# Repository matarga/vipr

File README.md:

# What is VIPR?

Simply put, VIPR is a open source radio node designed and built around North American mesh communication over LoRa built off of an ESP32-S3 platform. Put less simply, VIPR is another ESP32 development board focused more on frontend, hardware, and size. The project aims to create a small, pocketable radio node that can run independently. Currently the procsessing power of it's latest version (2.0) can only handle small workloads and can only run a Real Time OS in comparison to a fully fledged computer.

**VIPR is currently in Alpha testing, soon to be beta!**

I'm planning on spinning this project idea and base into another, thinking aboutthe name of ProtopadZero

## Current Revision

Currently the board packs a 19mm wide footprint without a screen. The end is equipped with an SMA conector for easy antenna swaps and the side boasts an onboard PCB wifi antenna tied to the ESP32-MINI-1 module.

Future revisions intend to add a screen and interactives to the board to further refine the frontend, all that is needed after that is software and a case!

### Changelog

```
* Redid a proper BOM
    * This included sizing and components selection
* Added back the CH340X
* Reverted to old "pen" form factor
* Created a new "lopsided" board end 
* Added a screen header
* Fixed a regulator issue on the radio portion
* bundled CAD files into production folders <=2.1
* Added JTAG test pads for rev 2.1.1
```

## Docs

Docs will be coming soon!
<br>

## Versioning system

The project follows a versioning system of major and minor. The first number in the version is the board platform. Whenever the board is fully redone a new major version will be released. Whenever the board has a small tweak to an existing platform version the second number behind the first will be bumped up by one.

A board version of say, 2.1 would indicate platform version 2 with one tweak of the original version 2.0.

#### Latest Journal as of July 28th

For revision 2.1. I introduced a versioning system of major and minor.
 What's new in 2.1?

Mounting holes for M2 screws on the left side of the board and a header connection for a screen. the schematics now include test points for serial, power, and JTAG soon to be onboard for revision 2.2.

Some issues were included in revision 2 that would prevent stable operation of the radio caused by a faulty connection between the regulator for the SX1262 and the inductor managing it.

That's all.

-Matias

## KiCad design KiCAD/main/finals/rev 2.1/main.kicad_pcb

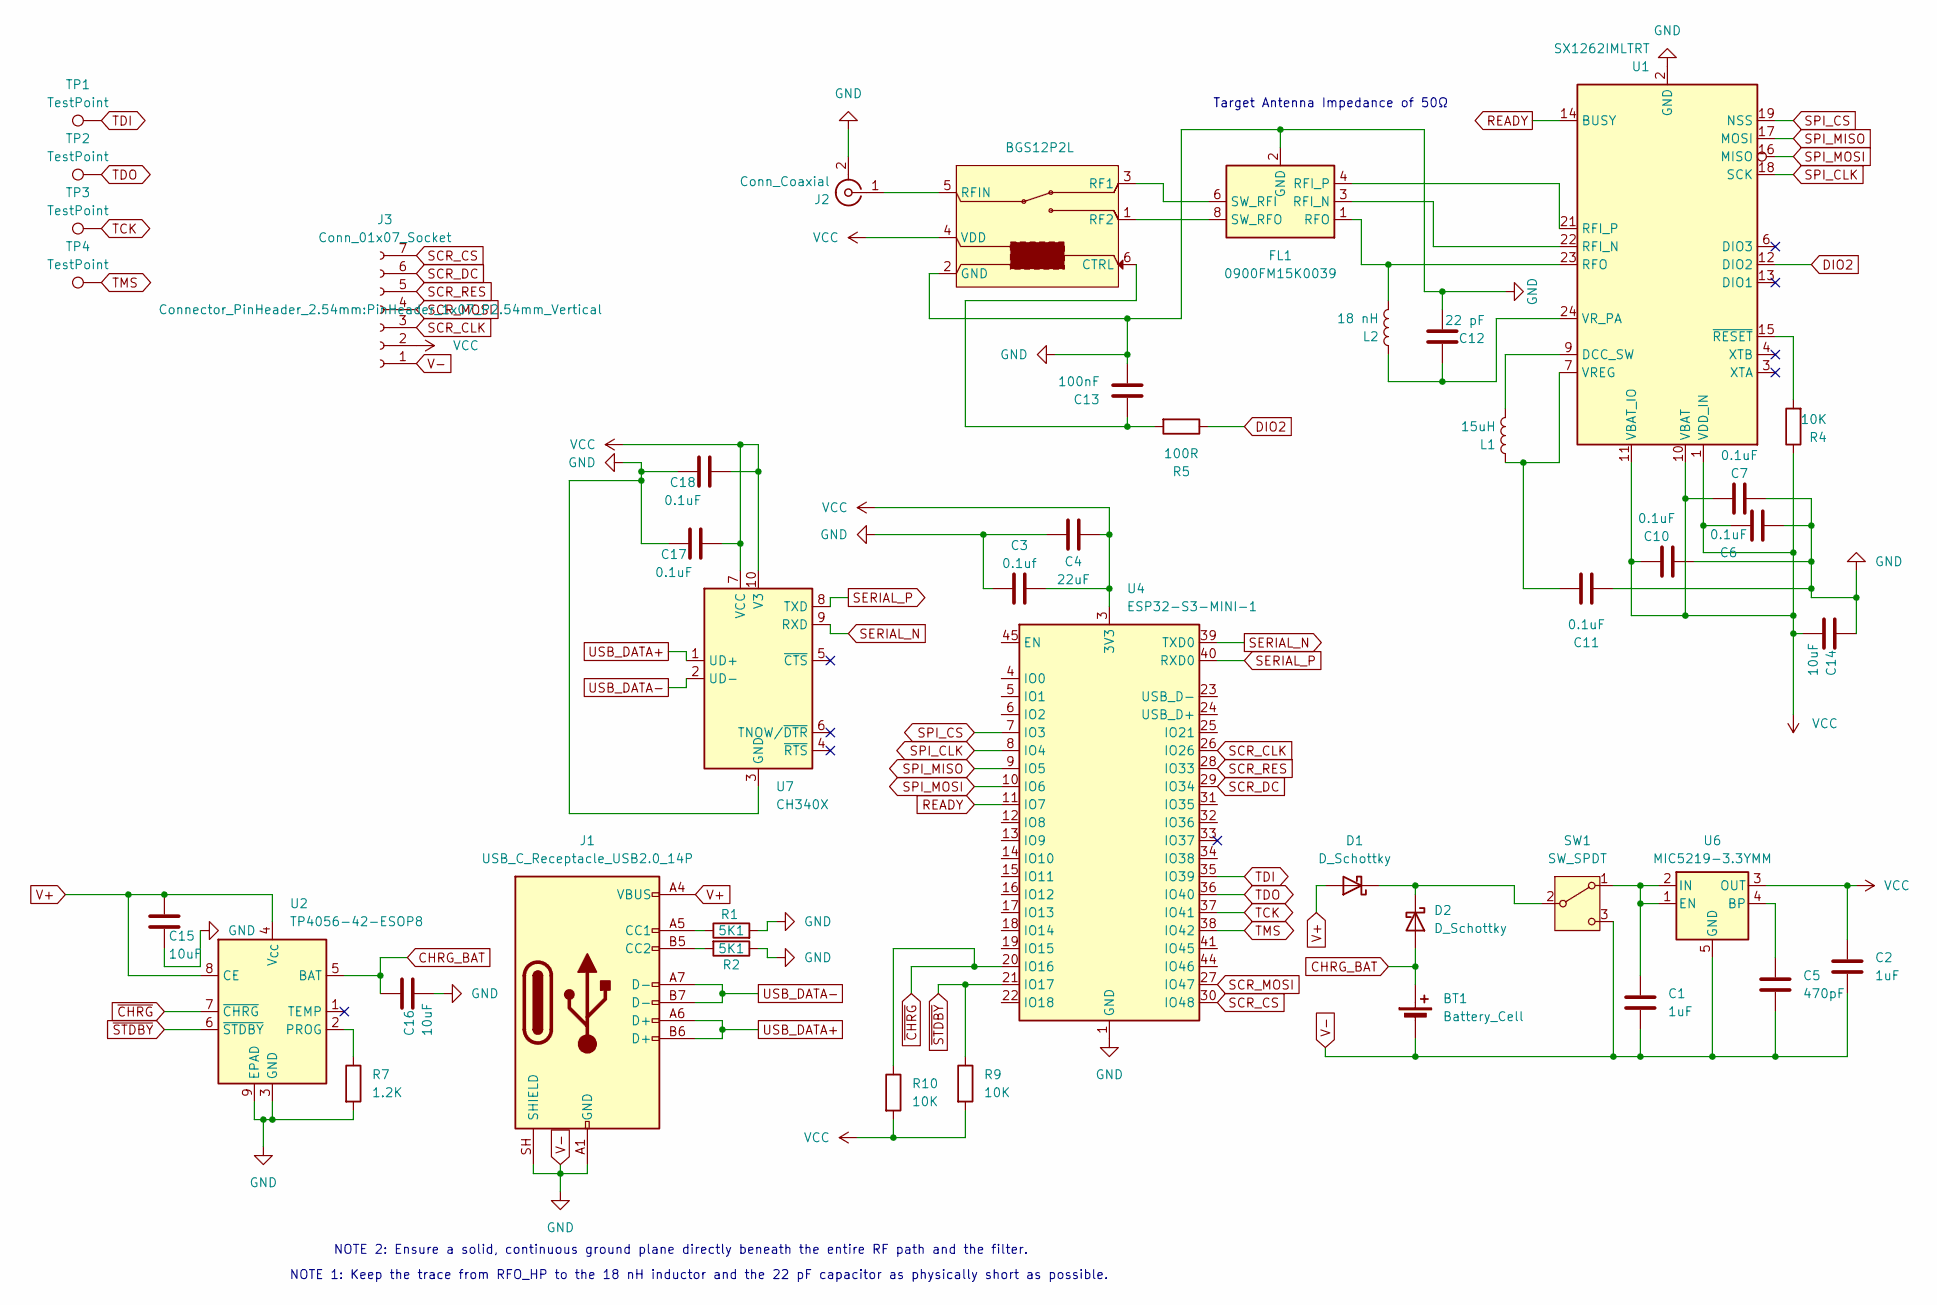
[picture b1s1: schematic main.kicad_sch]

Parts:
BT1: Battery_Cell; JST_PH_S2B-PH-K_1x02_P2.00mm_Horizontal; LCSC Part # C265094
C1, C2: 1uF; C_0603_1608Metric; LCSC Part # C15849
C3: 0.1uf; C_0402_1005Metric; LCSC Part # C1525
C4: 22uF; C_0805_2012Metric; LCSC Part # C45783
C5: 470pF; C_0603_1608Metric; LCSC Part # C1620
C6, C7, C10, C11, C17, C18: 0.1uF; C_0402_1005Metric; LCSC Part # C1525
C12: 22 pF; C_0603_1608Metric; LCSC Part # C1653
C13: 100nF; C_0402_1005Metric; LCSC Part # C1525
C14, C15, C16: 10uF; C_0603_1608Metric; LCSC Part # C19702
D1, D2: D_Schottky; D_SOD-323; LCSC Part # C191023
FL1: 0900FM15K0039; Balun_Johanson_0900FM15K0039
J1: USB_C_Receptacle_USB2.0_14P; USB_C_Receptacle_GCT_USB4110; LCSC Part # C2765186
J2: Conn_Coaxial; SMA_Amphenol_132289_EdgeMount; LCSC Part # C3039673
J3: Conn_01x07_Socket; PinHeader_1x07_P2.54mm_Vertical
L1: 15uH; L_0805_2012Metric; LCSC Part # C383402
L2: 18 nH; L_0603_1608Metric; LCSC Part # C19721138
R1, R2: 5K1; R_0603_1608Metric; LCSC Part # C23186
R4, R9, R10: 10K; R_0603_1608Metric; LCSC Part # C25804
R5: 100R; R_0402_1005Metric; LCSC Part # C25076
R7: 1.2K; R_0603_1608Metric; LCSC Part # C22765
SW1: SW_SPDT; SSSS810701; LCSC Part # C97433
TP1, TP2, TP3, TP4: TestPoint; TestPoint_Pad_1.5x1.5mm
U1: SX1262IMLTRT; QFN-24-1EP_4x4mm_P0.5mm_EP2.6x2.6mm; LCSC Part # C191341
U2: TP4056-42-ESOP8; SOIC-8-1EP_3.9x4.9mm_P1.27mm_EP2.41x3.3mm_ThermalVias; LCSC Part # C16581
U3: BGS12P2L; Infineon_PG-TSNP-6-10_0.7x1.1mm_0.7x1.1mm_P0.4mm; LCSC Part # C3312945
U4: ESP32-S3-MINI-1; ESP32-S2-MINI-1
U6: MIC5219-3.3YMM; MSOP-8_3x3mm_P0.65mm; LCSC Part # C628154
U7: CH340X; MSOP-10_3x3mm_P0.5mm; LCSC Part # C3035748

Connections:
CHRG_BAT: BT1.1 (+), C16.2, D2.2 (A), U2.5 (BAT)
DIO2: R5.1, U1.12 (DIO2)
unnamed: D1.1 (K), D2.1 (K), SW1.2 (B)
unnamed: FL1.3 (RFI_N), U1.22 (RFI_N)
unnamed: FL1.4 (RFI_P), U1.21 (RFI_P)
unnamed: FL1.1 (RFO), L2.2, U1.23 (RFO)
unnamed: FL1.6 (SW_RFI), U3.3 (RF1)
unnamed: FL1.8 (SW_RFO), U3.1 (RF2)
unnamed: J1.A5 (CC1), R1.1
unnamed: J1.B5 (CC2), R2.2
unnamed: J2.1 (In), U3.5 (RFIN)
unnamed: C1.2, SW1.1 (A), U6.1 (EN), U6.2 (IN)
unnamed: L1.2, U1.9 (DCC_SW)
unnamed: C11.2, L1.1, U1.7 (VREG)
unnamed: C12.1, L2.1, U1.24 (VR_PA)
unnamed: R4.2, U1.15 (~RESET)
unnamed: R7.1, U2.2 (PROG)
unnamed: C13.1, R5.2, U3.6 (CTRL)
unnamed: C5.1, U6.4 (BP)
READY: U1.14 (BUSY), U4.11 (IO7)
SCR_CLK: J3.3, U4.26 (IO26)
SCR_CS: J3.7, U4.30 (IO48)
SCR_DC: J3.6, U4.29 (IO34)
SCR_MOSI: J3.4, U4.27 (IO47)
SCR_RES: J3.5, U4.28 (IO33)
SERIAL_N: U4.39 (TXD0), U7.9 (RXD)
SERIAL_P: U4.40 (RXD0), U7.8 (TXD)
SPI_CLK: U1.18 (SCK), U4.8 (IO4)
SPI_CS: U1.19 (NSS), U4.7 (IO3)
SPI_MISO: U1.17 (MOSI), U4.9 (IO5)
SPI_MOSI: U1.16 (MISO), U4.10 (IO6)
TCK: TP3.1 (1_1), U4.37 (IO41)
TDI: TP1.1 (1_1), U4.35 (IO39)
TDO: TP2.1 (1_1), U4.36 (IO40)
TMS: TP4.1 (1_1), U4.38 (IO42)
USB_DATA+: J1.A6 (D+), J1.B6 (D+), U7.1 (UD+)
USB_DATA-: J1.A7 (D-), J1.B7 (D-), U7.2 (UD-)
V+: C15.1, D1.2 (A), J1.A4 (VBUS), J1.A9 (VBUS), J1.B4 (VBUS), J1.B9 (VBUS), U2.4 (V_{CC}), U2.8 (CE)
V-: BT1.2 (-), C1.1, C2.1, C3.1, C4.1, C5.2, C6.2, C7.2, C10.2, C11.1, C12.2, C13.2, C14.1, C15.2, C16.1, C17.1, C18.1, FL1.2 (GND), FL1.5 (GND), FL1.7 (GND), FL1.9 (GND), FL1.10 (GND), J1.A1 (GND), J1.A12 (GND), J1.B1 (GND), J1.B12 (GND), J1.SH (SHIELD), J2.2 (Ext), J3.1, R1.2, R2.1, R7.2, SW1.3 (C), U1.2 (GND), U1.5 (GND), U1.8 (GND), U1.20 (GND), U1.25 (GND), U2.3 (GND), U2.9 (EPAD), U3.2 (GND), U4.1 (GND), U4.2 (GND), U4.42 (GND), U4.43 (GND), U4.46 (GND), U4.47 (GND), U4.48 (GND), U4.49 (GND), U4.50 (GND), U4.51 (GND), U4.52 (GND), U4.53 (GND), U4.54 (GND), U4.55 (GND), U4.56 (GND), U4.57 (GND), U4.58 (GND), U4.59 (GND), U4.60 (GND), U4.61 (GND), U4.62 (GND), U4.63 (GND), U4.64 (GND), U4.65 (GND), U6.5 (GND), U6.6 (GND), U6.7 (GND), U6.8 (GND), U7.3 (GND)
VCC: C2.2, C3.2, C4.2, C6.1, C7.1, C10.1, C14.2, C17.2, C18.2, J3.2, R4.1, R9.2, R10.2, U1.1 (VDD_IN), U1.10 (VBAT), U1.11 (VBAT_IO), U3.4 (VDD), U4.3 (3V3), U6.3 (OUT), U7.7 (VCC), U7.10 (V3)
~CHRG: R10.1, U2.7 (~CHRG), U4.20 (IO16)
~STDBY: R9.1, U2.6 (~STDBY), U4.21 (IO17)

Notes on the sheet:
NOTE 1: Keep the trace from RFO_HP to the 18 nH inductor and the 22 pF capacitor as physically short as possible.
NOTE 2: Ensure a solid, continuous ground plane directly beneath the entire RF path and the filter.
Target Antenna Impedance of 50Ω

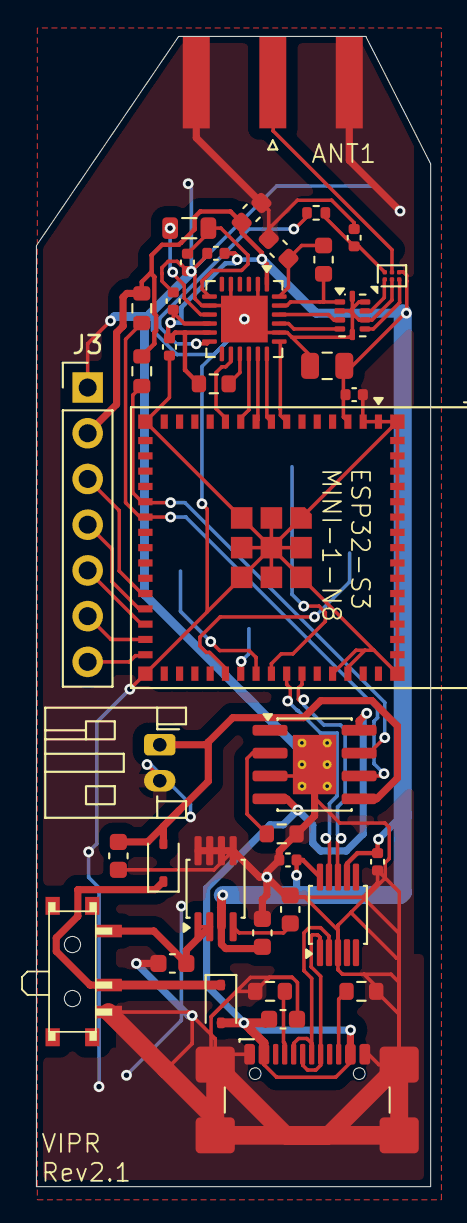
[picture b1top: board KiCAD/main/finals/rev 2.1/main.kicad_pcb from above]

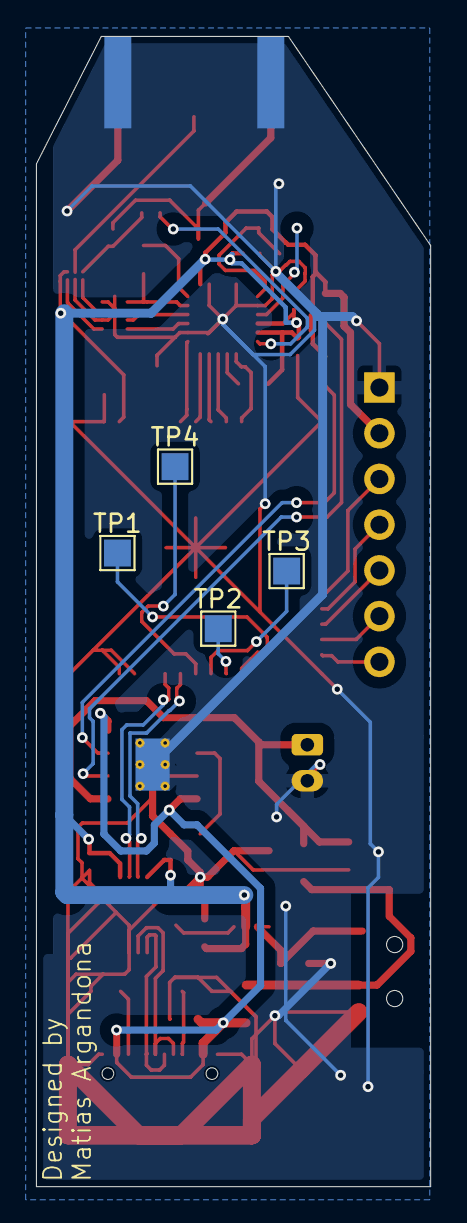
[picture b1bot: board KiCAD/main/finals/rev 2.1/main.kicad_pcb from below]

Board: 2 copper layers, 21.9 x 63.9 mm, 43 parts (4 on the bottom side), 42 nets.

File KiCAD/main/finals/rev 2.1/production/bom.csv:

Designator,Footprint,Quantity,Value,LCSC Part #
BT1,JST_PH_S2B-PH-K_1x02_P2.00mm_Horizontal,1,Battery_Cell,C265094
"C1, C2",0603,2,1uF,C15849
"C10, C11, C17, C18, C3, C6, C7",0402,7,0.1uF,C1525
C12,0603,1,22 pF,C1653
C13,0402,1,100nF,C1525
"C14, C15, C16",0603,3,10uF,C19702
C4,0805,1,22uF,C45783
C5,0603,1,470pF,C1620
"D1, D2",D_SOD-323,2,D_Schottky,C191023
J1,USB_C_Receptacle_GCT_USB4110,1,USB_C_Receptacle_USB2.0_14P,C2765186
J2,SMA_Amphenol_132289_EdgeMount,1,Conn_Coaxial,C3039673
J3,PinHeader_1x07_P2.54mm_Vertical,1,Conn_01x07_Socket,
L1,0805,1,15uH,C383402
L2,0603,1,18 nH,C19721138
"R1, R2",0603,2,5K1,C23186
"R10, R4, R9",0603,3,10K,C25804
R5,0402,1,100R,C25076
R7,0603,1,1.2K,C22765
SW1,SSSS810701,1,SW_SPDT,C97433
"TP1, TP2, TP3, TP4",TestPoint_Pad_1.5x1.5mm,4,TestPoint,
U1,QFN-24-1EP_4x4mm_P0.5mm_EP2.6x2.6mm,1,SX1262IMLTRT,C191341
U2,SOIC-8-1EP_3.9x4.9mm_P1.27mm_EP2.41x3.3mm_ThermalVias,1,TP4056-42-ESOP8,C16581
U3,Infineon_PG-TSNP-6-10_0.7x1.1mm_0.7x1.1mm_P0.4mm,1,BGS12P2L,C3312945
U6,MSOP-8_3x3mm_P0.65mm,1,MIC5219-3.3YMM,C628154
U7,MSOP-10_3x3mm_P0.5mm,1,CH340X,C3035748

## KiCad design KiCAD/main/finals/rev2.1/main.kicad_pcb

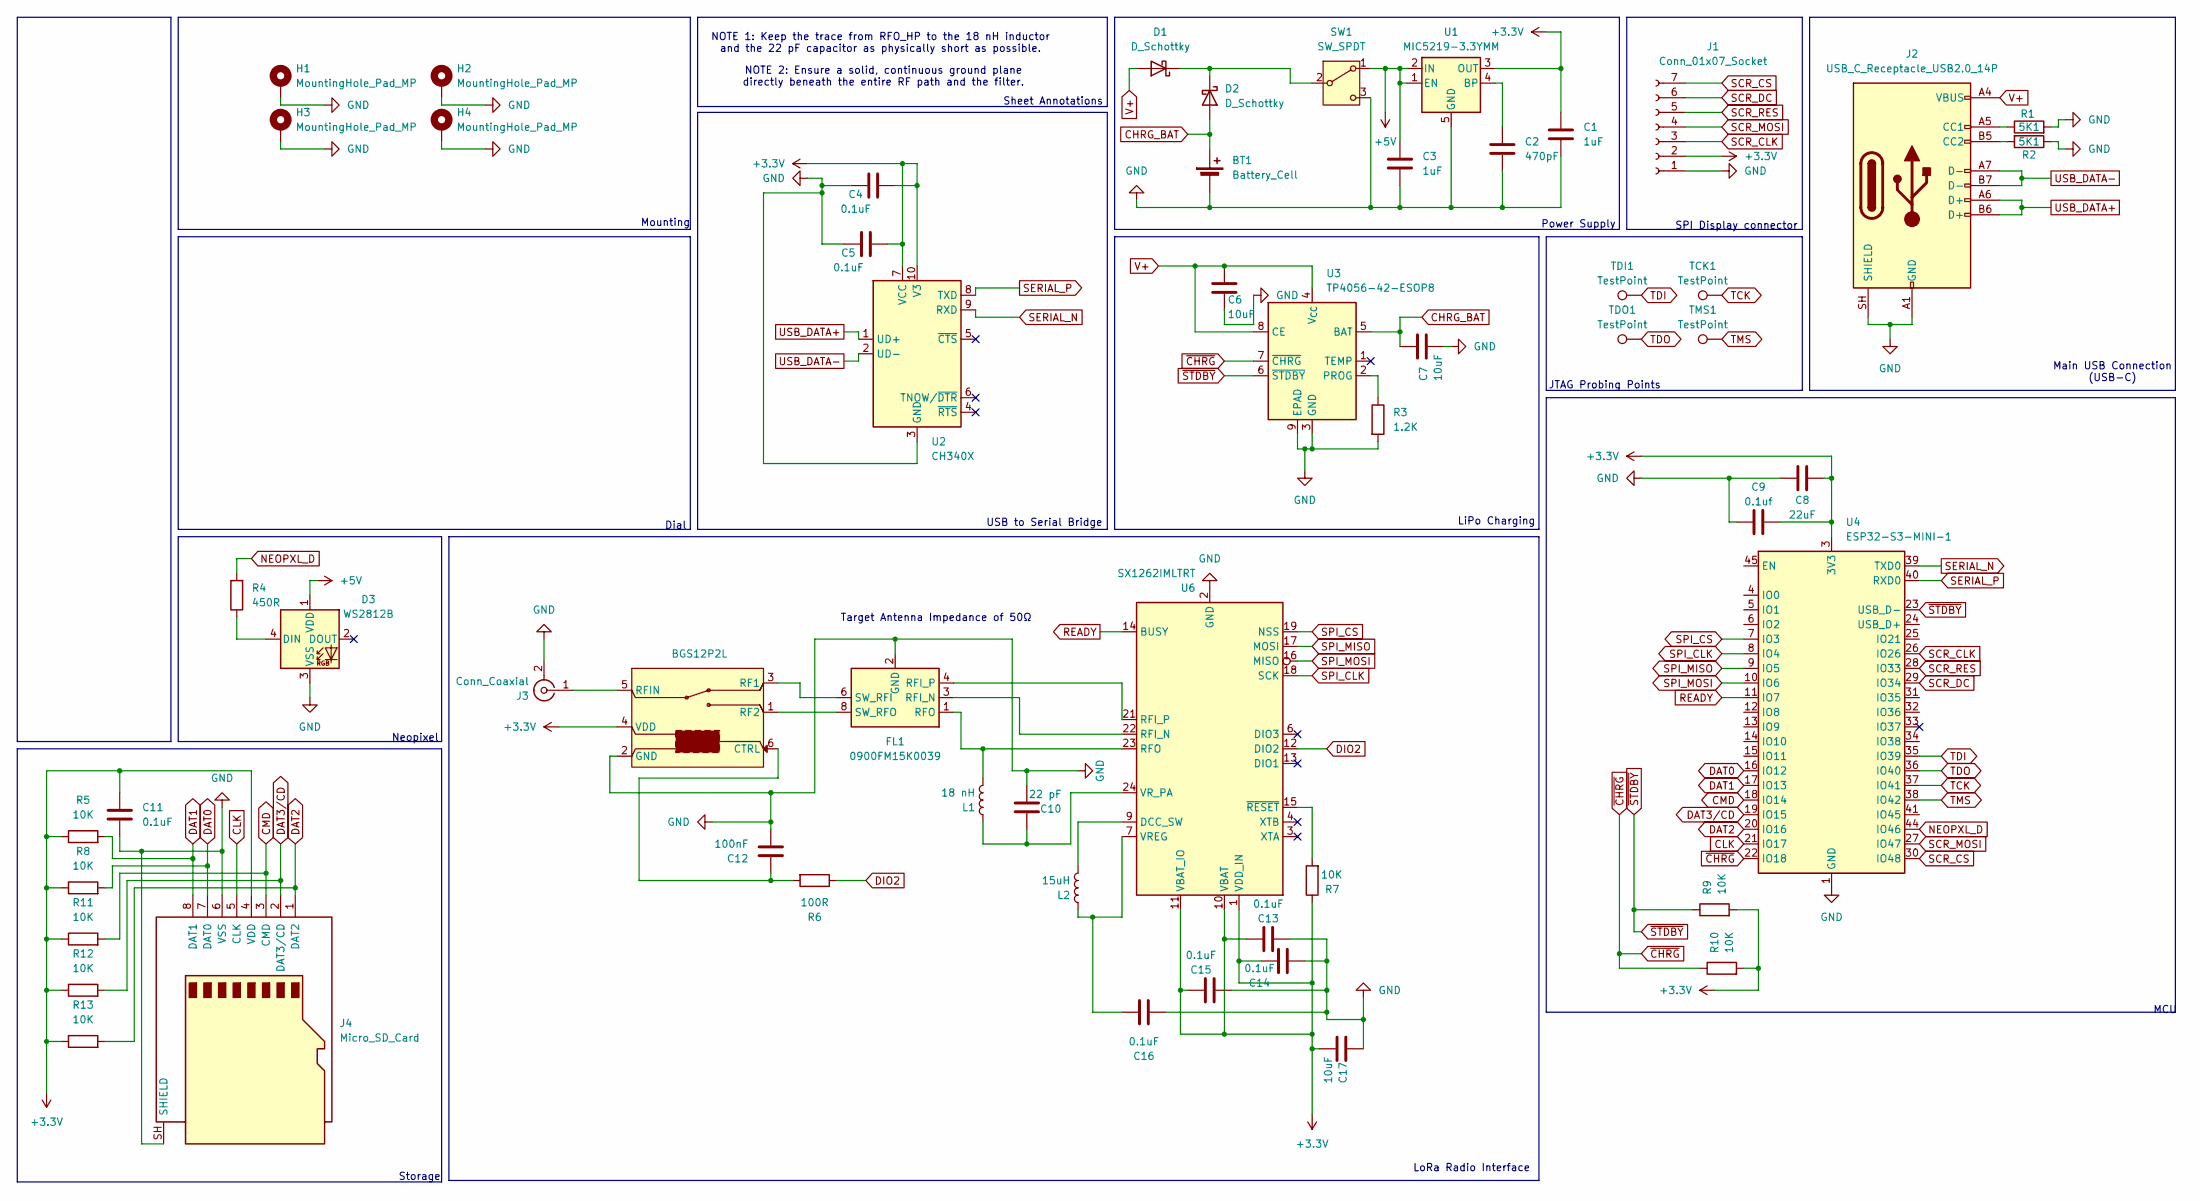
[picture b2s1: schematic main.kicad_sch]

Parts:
BT1: Battery_Cell; JST_PH_S2B-PH-K_1x02_P2.00mm_Horizontal; LCSC Part # C265094
C1, C3: 1uF; C_0603_1608Metric; LCSC Part # C77386
C2: 470pF; C_0603_1608Metric; LCSC Part # C1620
C4, C5, C11, C13, C14, C15, C16: 0.1uF; C_0402_1005Metric; LCSC Part # C1525
C6, C7, C17: 10uF; C_0603_1608Metric; LCSC Part # C19702
C8: 22uF; C_0805_2012Metric; LCSC Part # C45783
C9: 0.1uf; C_0402_1005Metric; LCSC Part # C1525
C10: 22 pF; C_0603_1608Metric; LCSC Part # C1653
C12: 100nF; C_0402_1005Metric; LCSC Part # C1525
D1, D2: D_Schottky; D_SOD-323; LCSC Part # C191023
D3: WS2812B; LED_WS2812B_PLCC4_5.0x5.0mm_P3.2mm; LCSC Part # C114586
FL1: 0900FM15K0039; Balun_Johanson_0900FM15K0039; LCSC Part # C7434807
H1, H2, H3, H4: MountingHole_Pad_MP; MountingHole_2.5mm_Pad_TopBottom
J1: Conn_01x07_Socket; PinHeader_1x07_P2.54mm_Vertical
J2: USB_C_Receptacle_USB2.0_14P; USB_C_Receptacle_GCT_USB4110; LCSC Part # C2765186
J3: Conn_Coaxial; SMA_Amphenol_132289_EdgeMount; LCSC Part # C3039673
J4: Micro_SD_Card; SIM-SMD_8P-1040310811; LCSC Part # C585350
L1: 18 nH; L_0603_1608Metric; LCSC Part # C19721138
L2: 15uH; L_0805_2012Metric; LCSC Part # C383402
R1, R2: 5K1; R_0603_1608Metric; LCSC Part # C23186
R3: 1.2K; R_0603_1608Metric; LCSC Part # C22765
R4: 450R; R_0402_1005Metric; LCSC Part # C186129
R5, R7, R8, R9, R10, R11, R12, R13: 10K; R_0603_1608Metric; LCSC Part # C2961367
R6: 100R; R_0402_1005Metric; LCSC Part # C25076
SW1: SW_SPDT; SSSS810701; LCSC Part # C97433
TCK1: TestPoint; TestPoint_Pad_1.5x1.5mm
TDI1: TestPoint; TestPoint_Pad_1.5x1.5mm
TDO1: TestPoint; TestPoint_Pad_1.5x1.5mm
TMS1: TestPoint; TestPoint_Pad_1.5x1.5mm
U1: MIC5219-3.3YMM; MSOP-8_3x3mm_P0.65mm; LCSC Part # C628154
U2: CH340X; MSOP-10_3x3mm_P0.5mm; LCSC Part # C3035748
U3: TP4056-42-ESOP8; SOIC-8-1EP_3.9x4.9mm_P1.27mm_EP2.41x3.3mm_ThermalVias; LCSC Part # C16581
U4: ESP32-S3-MINI-1; ESP32-S2-MINI-1; LCSC Part # C2913206
U5: BGS12P2L; Infineon_PG-TSNP-6-10_0.7x1.1mm_0.7x1.1mm_P0.4mm; LCSC Part # C3312945
U6: SX1262IMLTRT; QFN-24-1EP_4x4mm_P0.5mm_EP2.6x2.6mm; LCSC Part # C191341

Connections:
+5V: C3.2, D3.1 (VDD), SW1.1 (A), U1.1 (EN), U1.2 (IN)
CHRG_BAT: BT1.1 (+), C7.2, D2.2 (A), U3.5 (BAT)
CLK: J4.5 (CLK), U4.21 (IO17)
CMD: J4.3 (CMD), R11.2, U4.18 (IO14)
DAT0: J4.7 (DAT0), R8.2, U4.16 (IO12)
DAT1: J4.8 (DAT1), R5.2, U4.17 (IO13)
DAT2: J4.1 (DAT2), R13.2, U4.20 (IO16)
DAT3/CD: J4.2 (DAT3/CD), R12.2, U4.19 (IO15)
DIO2: R6.1, U6.12 (DIO2)
GND: BT1.2 (-), C1.1, C2.2, C3.1, C4.1, C5.1, C6.2, C7.1, C8.1, C9.1, C10.2, C11.1, C12.2, C13.2, C14.2, C15.2, C16.1, C17.1, D3.3 (VSS), FL1.2 (GND), FL1.5 (GND), FL1.7 (GND), FL1.9 (GND), FL1.10 (GND), H1.MP, H2.MP, H3.MP, H4.MP, J1.1, J2.A1 (GND), J2.A12 (GND), J2.B1 (GND), J2.B12 (GND), J2.SH (SHIELD), J3.2 (Ext), J4.6 (VSS), J4.SH (SHIELD), R1.2, R2.1, R3.2, SW1.3 (C), U1.5 (GND), U1.6 (GND), U1.7 (GND), U1.8 (GND), U2.3 (GND), U3.3 (GND), U3.9 (EPAD), U4.1 (GND), U4.2 (GND), U4.42 (GND), U4.43 (GND), U4.46 (GND), U4.47 (GND), U4.48 (GND), U4.49 (GND), U4.50 (GND), U4.51 (GND), U4.52 (GND), U4.53 (GND), U4.54 (GND), U4.55 (GND), U4.56 (GND), U4.57 (GND), U4.58 (GND), U4.59 (GND), U4.60 (GND), U4.61 (GND), U4.62 (GND), U4.63 (GND), U4.64 (GND), U4.65 (GND), U5.2 (GND), U6.2 (GND), U6.5 (GND), U6.8 (GND), U6.20 (GND), U6.25 (GND)
NEOPXL_D: R4.2, U4.44 (IO46)
unnamed: D1.1 (K), D2.1 (K), SW1.2 (B)
unnamed: D3.4 (DIN), R4.1
unnamed: FL1.3 (RFI_N), U6.22 (RFI_N)
unnamed: FL1.4 (RFI_P), U6.21 (RFI_P)
unnamed: FL1.1 (RFO), L1.2, U6.23 (RFO)
unnamed: FL1.6 (SW_RFI), U5.3 (RF1)
unnamed: FL1.8 (SW_RFO), U5.1 (RF2)
unnamed: J2.A5 (CC1), R1.1
unnamed: J2.B5 (CC2), R2.2
unnamed: J3.1 (In), U5.5 (RFIN)
unnamed: C2.1, U1.4 (BP)
unnamed: R3.1, U3.2 (PROG)
unnamed: C12.1, R6.2, U5.6 (CTRL)
unnamed: L2.2, U6.9 (DCC_SW)
unnamed: C16.2, L2.1, U6.7 (VREG)
unnamed: C10.1, L1.1, U6.24 (VR_PA)
unnamed: R7.2, U6.15 (~RESET)
READY: U4.11 (IO7), U6.14 (BUSY)
SCR_CLK: J1.3, U4.26 (IO26)
SCR_CS: J1.7, U4.30 (IO48)
SCR_DC: J1.6, U4.29 (IO34)
SCR_MOSI: J1.4, U4.27 (IO47)
SCR_RES: J1.5, U4.28 (IO33)
SERIAL_N: U2.9 (RXD), U4.39 (TXD0)
SERIAL_P: U2.8 (TXD), U4.40 (RXD0)
SPI_CLK: U4.8 (IO4), U6.18 (SCK)
SPI_CS: U4.7 (IO3), U6.19 (NSS)
SPI_MISO: U4.9 (IO5), U6.17 (MOSI)
SPI_MOSI: U4.10 (IO6), U6.16 (MISO)
TCK: TCK1.1 (1_1), U4.37 (IO41)
TDI: TDI1.1 (1_1), U4.35 (IO39)
TDO: TDO1.1 (1_1), U4.36 (IO40)
TMS: TMS1.1 (1_1), U4.38 (IO42)
USB_DATA+: J2.A6 (D+), J2.B6 (D+), U2.1 (UD+)
USB_DATA-: J2.A7 (D-), J2.B7 (D-), U2.2 (UD-)
V+: C6.1, D1.2 (A), J2.A4 (VBUS), J2.A9 (VBUS), J2.B4 (VBUS), J2.B9 (VBUS), U3.4 (V_{CC}), U3.8 (CE)
~CHRG: R10.1, U3.7 (~CHRG), U4.22 (IO18); also elsewhere on the board
~STDBY: R9.1, U3.6 (~STDBY), U4.23 (USB_D-); also elsewhere on the board

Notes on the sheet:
Storage
Sheet Annotations
NOTE 1: Keep the trace from RFO_HP to the 18 nH inductor and the 22 pF capacitor as physically short as possible.
NOTE 2: Ensure a solid, continuous ground plane directly beneath the entire RF path and the filter.
SPI Display connector
MCU
LiPo Charging
Main USB Connection (USB-C)
JTAG Probing Points
LoRa Radio Interface
Dial
Target Antenna Impedance of 50Ω
Power Supply
Neopixel
Mounting
USB to Serial Bridge

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
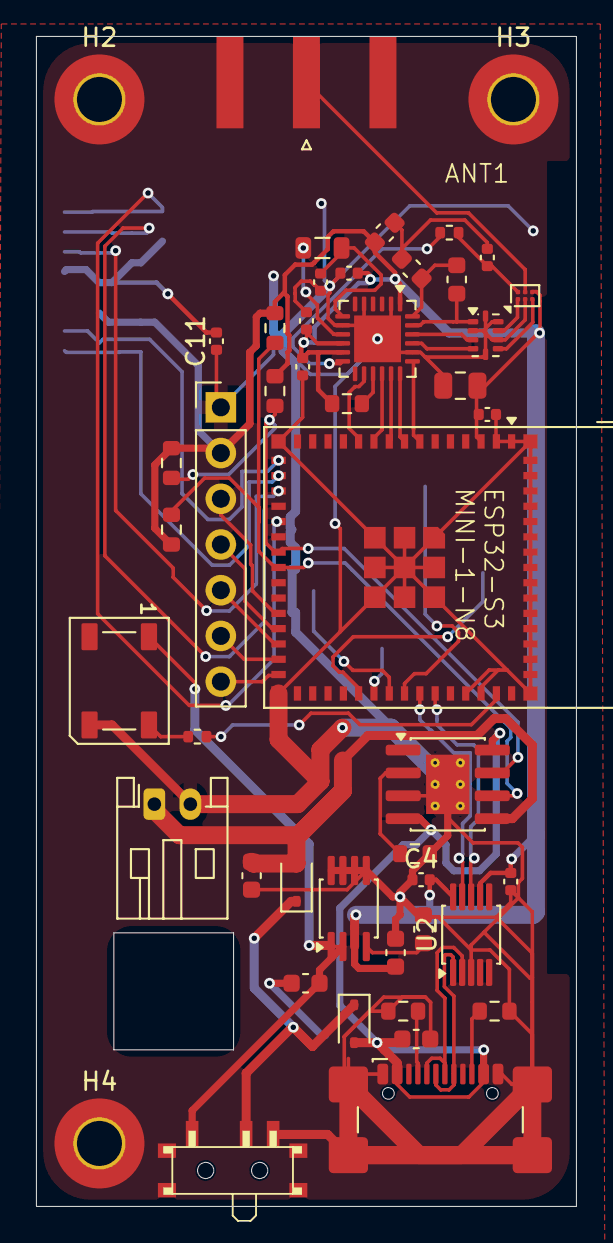
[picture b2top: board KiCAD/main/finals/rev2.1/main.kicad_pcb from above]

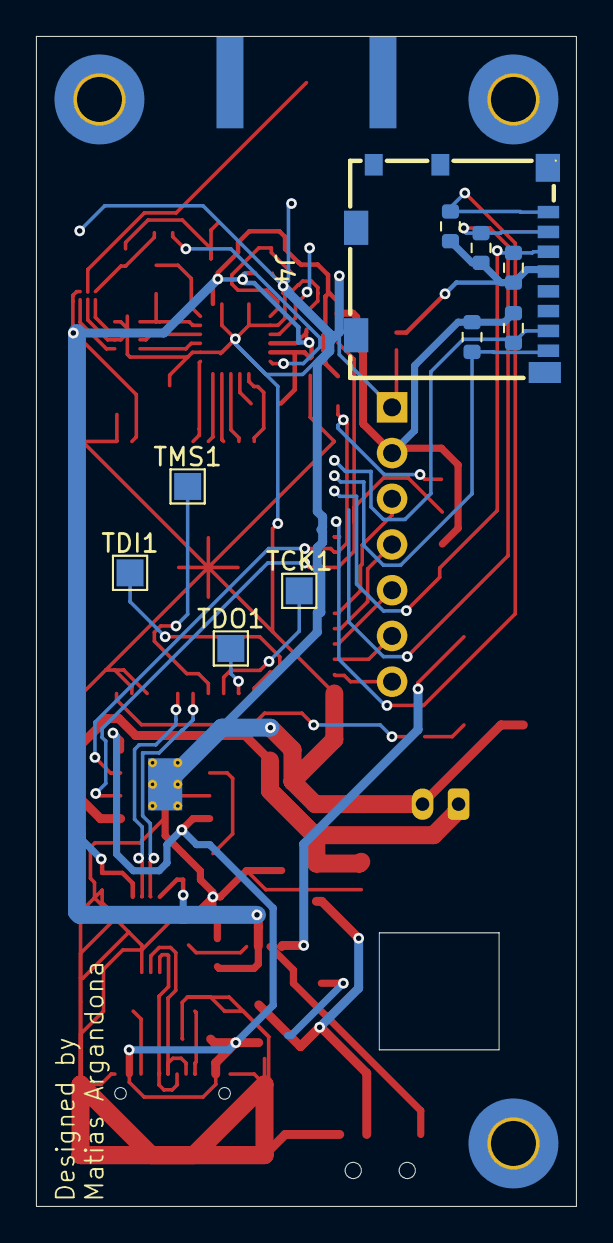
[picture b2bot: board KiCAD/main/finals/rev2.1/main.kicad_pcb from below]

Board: 2 copper layers, 30.0 x 65.0 mm, 57 parts (10 on the bottom side), 51 nets.

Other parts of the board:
R9#2, R10#2: 10K; R_0603_1608Metric

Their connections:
~CHRG: R10#2.1; also elsewhere on the board
~STDBY: R9#2.1; also elsewhere on the board

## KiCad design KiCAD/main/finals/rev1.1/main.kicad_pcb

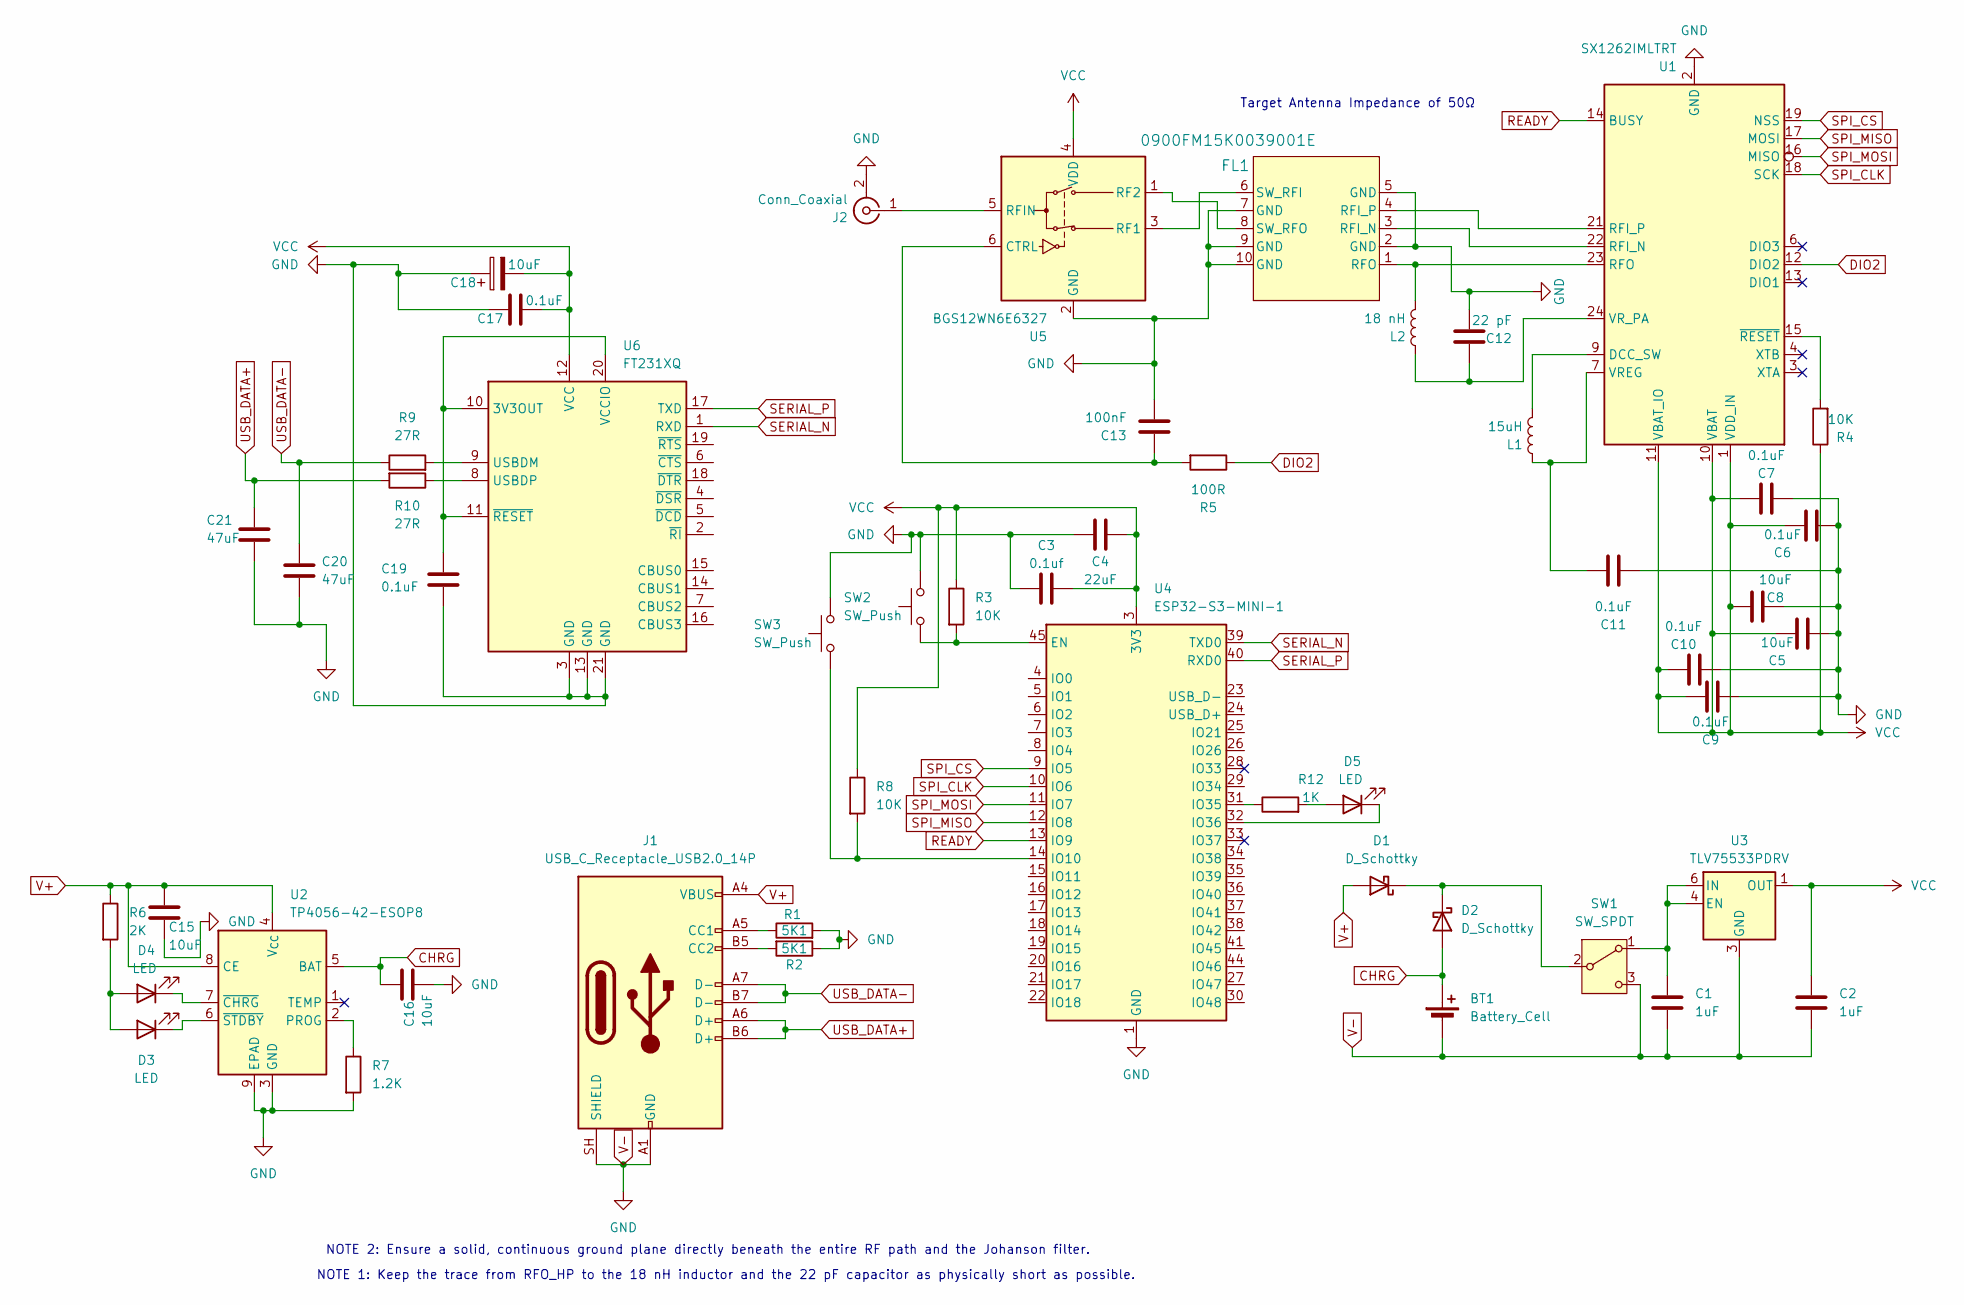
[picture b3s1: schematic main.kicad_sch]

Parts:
BT1: Battery_Cell; JST_PH_S2B-PH-K_1x02_P2.00mm_Horizontal
C1, C2: 1uF; C_01005_0402Metric
C3: 0.1uf; C_01005_0402Metric
C4: 22uF; C_01005_0402Metric
C5, C8, C15, C16: 10uF; C_01005_0402Metric
C6, C7, C9, C10, C11, C17, C19: 0.1uF; C_01005_0402Metric
C12: 22 pF; C_01005_0402Metric
C13: 100nF; C_01005_0402Metric
C18: 10uF; CP_EIA-1608-08_AVX-J
C20, C21: 47uF; C_01005_0402Metric
D1, D2: D_Schottky; D_01005_0402Metric
D3, D4, D5: LED; LED_0402_1005Metric
FL1: 0900FM15K0039001E; 0900FM15K0039001E_JOT-L
J1: USB_C_Receptacle_USB2.0_14P; USB_C_Receptacle_GCT_USB4110
J2: Conn_Coaxial; SMA_Amphenol_132289_EdgeMount
L1: 15uH; L_01005_0402Metric
L2: 18 nH; L_01005_0402Metric
R1, R2: 5K1; R_01005_0402Metric
R3, R4, R8: 10K; R_01005_0402Metric
R5: 100R; R_01005_0402Metric
R6: 2K; R_01005_0402Metric
R7: 1.2K; R_01005_0402Metric
R9, R10: 27R; R_01005_0402Metric
R12: 1K; R_01005_0402Metric
SW1: SW_SPDT; SW_SPDT_PCM12
SW2: SW_Push; SW_SPST_PTS810
SW3: SW_Push; SW_SPST_PTS645Sx43SMTR92
U1: SX1262IMLTRT; QFN-24-1EP_4x4mm_P0.5mm_EP2.6x2.6mm
U2: TP4056-42-ESOP8; SOIC-8-1EP_3.9x4.9mm_P1.27mm_EP2.41x3.3mm_ThermalVias
U3: TLV75533PDRV; WSON-6-1EP_2x2mm_P0.65mm_EP1x1.6mm
U4: ESP32-S3-MINI-1; ESP32-S2-MINI-1
U5: BGS12WN6E6327; Infineon_PG-TSNP-6-10_0.7x1.1mm_0.7x1.1mm_P0.4mm
U6: FT231XQ; QFN-20-1EP_4x4mm_P0.5mm_EP2.5x2.5mm

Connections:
CHRG: BT1.1 (+), C16.2, D2.2 (A), U2.5 (BAT)
DIO2: R5.1, U1.12 (DIO2)
unnamed: D1.1 (K), D2.1 (K), SW1.2 (B)
unnamed: D3.2 (A), D4.2 (A), R6.2
unnamed: D3.1 (K), U2.6 (~STDBY)
unnamed: D4.1 (K), U2.7 (~CHRG)
unnamed: D5.2 (A), R12.2
unnamed: D5.1 (K), U4.32 (IO36)
unnamed: FL1.3 (RFI_N), U1.22 (RFI_N)
unnamed: FL1.4 (RFI_P), U1.21 (RFI_P)
unnamed: FL1.1 (RFO), L2.2, U1.23 (RFO)
unnamed: FL1.6 (SW_RFI), U5.3 (RF1)
unnamed: FL1.8 (SW_RFO), U5.1 (RF2)
unnamed: J1.A5 (CC1), R1.1
unnamed: J1.B5 (CC2), R2.2
unnamed: J2.1 (In), U5.5 (RFIN)
unnamed: C1.2, SW1.1 (A), U3.4 (EN), U3.6 (IN)
unnamed: L1.2, U1.9 (DCC_SW)
unnamed: C11.2, L1.1, U1.7 (VREG)
unnamed: C12.1, L2.1, U1.24 (VR_PA)
unnamed: R4.2, U1.15 (~RESET)
unnamed: R7.1, U2.2 (PROG)
unnamed: R3.2, SW2.1, U4.45 (EN)
unnamed: R8.2, SW3.1, U4.14 (IO10)
unnamed: R12.1, U4.31 (IO35)
unnamed: C13.1, R5.2, U5.6 (CTRL)
unnamed: C19.2, U6.10 (3V3OUT), U6.11 (~RESET), U6.20 (VCCIO)
unnamed: R9.2, U6.9 (USBDM)
unnamed: R10.1, U6.8 (USBDP)
READY: U1.14 (BUSY), U4.13 (IO9)
SERIAL_N: U4.39 (TXD0), U6.1 (RXD)
SERIAL_P: U4.40 (RXD0), U6.17 (TXD)
SPI_CLK: U1.18 (SCK), U4.10 (IO6)
SPI_CS: U1.19 (NSS), U4.9 (IO5)
SPI_MISO: U1.17 (MOSI), U4.12 (IO8)
SPI_MOSI: U1.16 (MISO), U4.11 (IO7)
USB_DATA+: C21.1, J1.A6 (D+), J1.B6 (D+), R10.2
USB_DATA-: C20.1, J1.A7 (D-), J1.B7 (D-), R9.1
V+: C15.1, D1.2 (A), J1.A4 (VBUS), J1.A9 (VBUS), J1.B4 (VBUS), J1.B9 (VBUS), R6.1, U2.4 (V_{CC}), U2.8 (CE)
V-: BT1.2 (-), C1.1, C2.1, C3.1, C4.1, C5.2, C6.2, C7.2, C8.2, C9.2, C10.2, C11.1, C12.2, C13.2, C15.2, C16.1, C17.1, C18.1, C19.1, C20.2, C21.2, FL1.2 (GND), FL1.5 (GND), FL1.7 (GND), FL1.9 (GND), FL1.10 (GND), J1.A1 (GND), J1.A12 (GND), J1.B1 (GND), J1.B12 (GND), J1.SH (SHIELD), J2.2 (Ext), R1.2, R2.1, R7.2, SW1.3 (C), SW2.2, SW3.2, U1.2 (GND), U1.5 (GND), U1.8 (GND), U1.20 (GND), U1.25 (GND), U2.3 (GND), U2.9 (EPAD), U3.3 (GND), U3.7 (GND), U4.1 (GND), U4.2 (GND), U4.42 (GND), U4.43 (GND), U4.46 (GND), U4.47 (GND), U4.48 (GND), U4.49 (GND), U4.50 (GND), U4.51 (GND), U4.52 (GND), U4.53 (GND), U4.54 (GND), U4.55 (GND), U4.56 (GND), U4.57 (GND), U4.58 (GND), U4.59 (GND), U4.60 (GND), U4.61 (GND), U4.62 (GND), U4.63 (GND), U4.64 (GND), U4.65 (GND), U5.2 (GND), U6.3 (GND), U6.13 (GND), U6.21 (GND)
VCC: C2.2, C3.2, C4.2, C5.1, C6.1, C7.1, C8.1, C9.1, C10.1, C17.2, C18.2, R3.1, R4.1, R8.1, U1.1 (VDD_IN), U1.10 (VBAT), U1.11 (VBAT_IO), U3.1 (OUT), U4.3 (3V3), U5.4 (VDD), U6.12 (VCC)

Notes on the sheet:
NOTE 1: Keep the trace from RFO_HP to the 18 nH inductor and the 22 pF capacitor as physically short as possible.
NOTE 2: Ensure a solid, continuous ground plane directly beneath the entire RF path and the Johanson filter.
Target Antenna Impedance of 50Ω

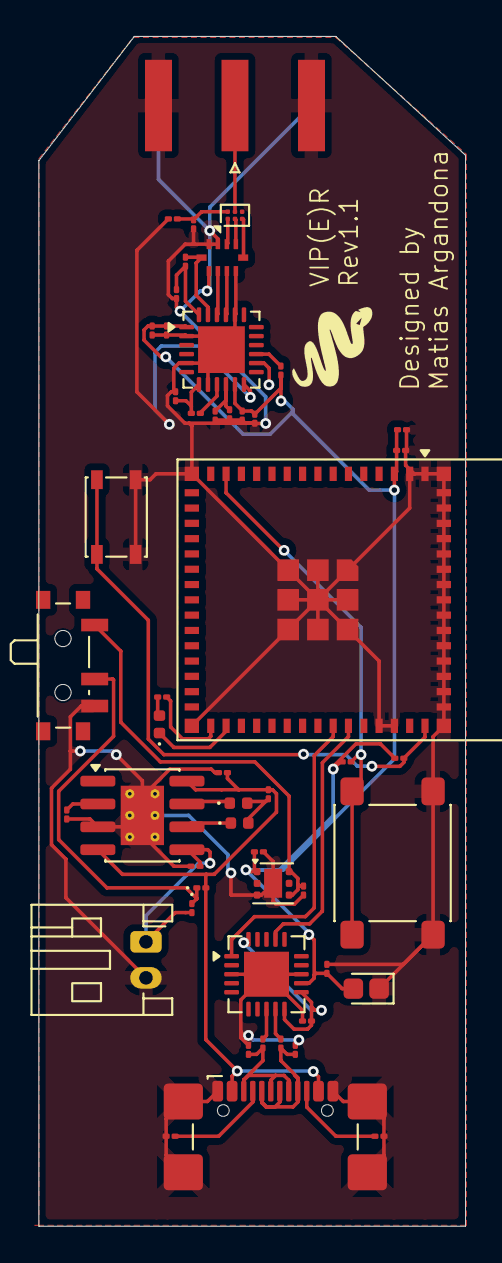
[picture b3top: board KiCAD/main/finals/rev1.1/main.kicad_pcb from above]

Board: 2 copper layers, 23.7 x 66.1 mm, 51 parts (0 on the bottom side), 41 nets.

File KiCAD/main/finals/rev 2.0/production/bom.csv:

Designator,Footprint,Quantity,Value,LCSC Part #
BT1,JST_PH_S2B-PH-K_1x02_P2.00mm_Horizontal,1,Battery_Cell,C265094
"C1, C2",0603,2,1uF,C15849
"C10, C11, C17, C18, C3, C6, C7",0402,7,0.1uF,C1525
C12,0603,1,22 pF,C1653
C13,0402,1,100nF,C1525
"C14, C15, C16",0603,3,10uF,C19702
C4,0805,1,22uF,C45783
C5,0603,1,470pF,C1620
"D1, D2",D_SOD-323,2,D_Schottky,C191023
J1,USB_C_Receptacle_GCT_USB4110,1,USB_C_Receptacle_USB2.0_14P,C2765186
J2,SMA_Amphenol_132289_EdgeMount,1,Conn_Coaxial,C3039673
L1,0805,1,15uH,C383402
L2,0603,1,18 nH,C19721138
"R1, R2",0603,2,5K1,C23186
"R10, R4, R9",0603,3,10K,C25804
R5,0402,1,100R,C25076
R7,0603,1,1.2K,C22765
SW1,SSSS810701,1,SW_SPDT,C97433
U1,QFN-24-1EP_4x4mm_P0.5mm_EP2.6x2.6mm,1,SX1262IMLTRT,C191341
U2,SOIC-8-1EP_3.9x4.9mm_P1.27mm_EP2.41x3.3mm_ThermalVias,1,TP4056-42-ESOP8,C16581
U3,Infineon_PG-TSNP-6-10_0.7x1.1mm_0.7x1.1mm_P0.4mm,1,BGS12P2L,C3312945
U6,MSOP-8_3x3mm_P0.65mm,1,MIC5219-3.3YMM,C628154
U7,MSOP-10_3x3mm_P0.5mm,1,CH340X,C3035748
Please use LCSC Parts
